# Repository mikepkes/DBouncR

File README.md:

The  D-BouncR is a 6-channel button debouncing board.

This board features:

* Independent Hardware Debouncing for up to 6 Buttons
* Adjustable debouncing parameters (change R and C values, examples will be in documentation)
* Protoboard Compatible (just drop it on your protoboard and pins should align for outputs and power)
* Adjustable High Voltage or Low Voltage default state with solderable jumpers per-channel.
* An attractive “D” shape
* Cheap & Reusable.
* Hand Solderable (even for beginners)
* Optional Button Pad with 6 Buttons

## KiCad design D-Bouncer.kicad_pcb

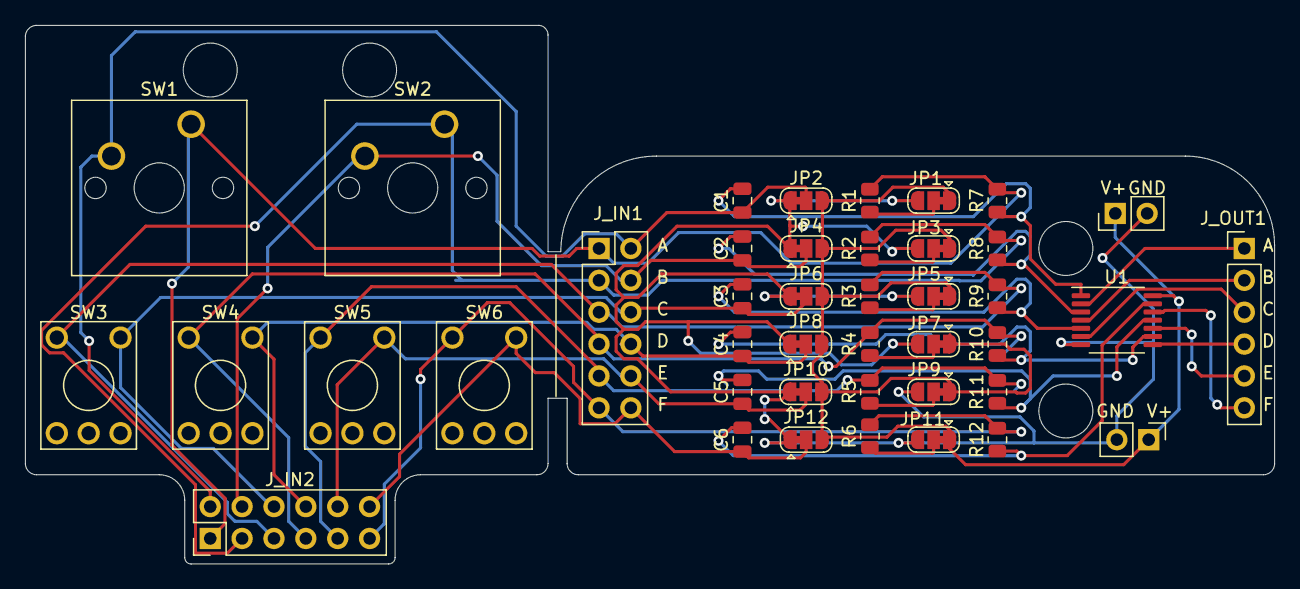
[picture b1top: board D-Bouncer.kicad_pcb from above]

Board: 2 copper layers, 99.6 x 42.9 mm, 42 parts (0 on the bottom side), 32 nets.

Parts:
C1, C2, C3, C4, C5, C6: C; C_0805_2012Metric
JP1, JP3, JP5, JP7, JP9, JP11: RestSelector; SolderJumper-3_P1.3mm_Bridged12_RoundedPad1.0x1.5mm
JP2, JP4, JP6, JP8, JP10, JP12: FilterSelector; SolderJumper-3_P1.3mm_Bridged12_RoundedPad1.0x1.5mm
J_IN1, J_IN2: Conn_02x06_Odd_Even; PinHeader_2x06_P2.54mm_Vertical
J_OUT1: Conn_01x06; PinHeader_1x06_P2.54mm_Vertical
J_PWR1, J_PWR2: Conn_01x02; PinHeader_1x02_P2.54mm_Vertical
R1, R2, R3, R4, R5, R6, R7, R8, R9, R10, R11, R12: R_US; R_0805_2012Metric
SW1, SW2: SW_SPST; SW_Cherry_MX_1.00u_PCB
SW3, SW4, SW5, SW6: SW_SPST; KSA_Tactile_SPST
U1: 74HC14; TSSOP-14_4.4x5mm_P0.65mm

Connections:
A: J_OUT1.1, U1.2
B: J_OUT1.2, U1.4
BTNA: J_IN1.1, J_IN2.1, R1.2, R7.2, SW1.1
BTNA_V: C1.1, JP2.2, J_IN1.2, J_IN2.2, SW1.2
BTNB: J_IN1.3, J_IN2.3, R2.2, R8.2, SW2.1
BTNB_V: C2.1, JP4.2, J_IN1.4, J_IN2.4, SW2.2
BTNC: J_IN1.5, J_IN2.5, R3.2, R9.2, SW3.1
BTNC_V: C3.1, JP6.2, J_IN1.6, J_IN2.6, SW3.2
BTND: J_IN1.7, J_IN2.7, R4.2, R10.2, SW4.1
BTND_V: C4.1, JP8.2, J_IN1.8, J_IN2.8, SW4.2
BTNE: J_IN1.9, J_IN2.9, R5.2, R11.2, SW5.1
BTNE_V: C5.1, JP10.2, J_IN1.10, J_IN2.10, SW5.2
BTNF: J_IN1.11, J_IN2.11, R6.2, R12.2, SW6.1
BTNF_V: C6.1, JP12.2, J_IN1.12, J_IN2.12, SW6.2
C: J_OUT1.3, U1.6
D: J_OUT1.4, U1.8
E: J_OUT1.5, U1.10
F: J_OUT1.6, U1.12
GND: JP1.3, JP2.1, JP3.3, JP4.1, JP5.3, JP6.1, JP7.3, JP8.1, JP9.3, JP10.1, JP11.3, JP12.1, J_PWR1.2, J_PWR2.2, U1.7
unnamed: C1.2, R7.1, U1.1
unnamed: C2.2, R8.1, U1.3
unnamed: C3.2, R9.1, U1.5
unnamed: C4.2, R10.1, U1.9
unnamed: C5.2, R11.1, U1.11
unnamed: C6.2, R12.1, U1.13
unnamed: JP1.2, R1.1
unnamed: JP3.2, R2.1
unnamed: JP5.2, R3.1
unnamed: JP7.2, R4.1
unnamed: JP9.2, R5.1
unnamed: JP11.2, R6.1
VCC: JP1.1, JP2.3, JP3.1, JP4.3, JP5.1, JP6.3, JP7.1, JP8.3, JP9.1, JP10.3, JP11.1, JP12.3, J_PWR1.1, J_PWR2.1, U1.14

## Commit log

2022-01-07 Adding Initial Readme
2022-01-07 Adding Front and Back PCB images.
2022-01-07 Adding PCB render to readme images.
